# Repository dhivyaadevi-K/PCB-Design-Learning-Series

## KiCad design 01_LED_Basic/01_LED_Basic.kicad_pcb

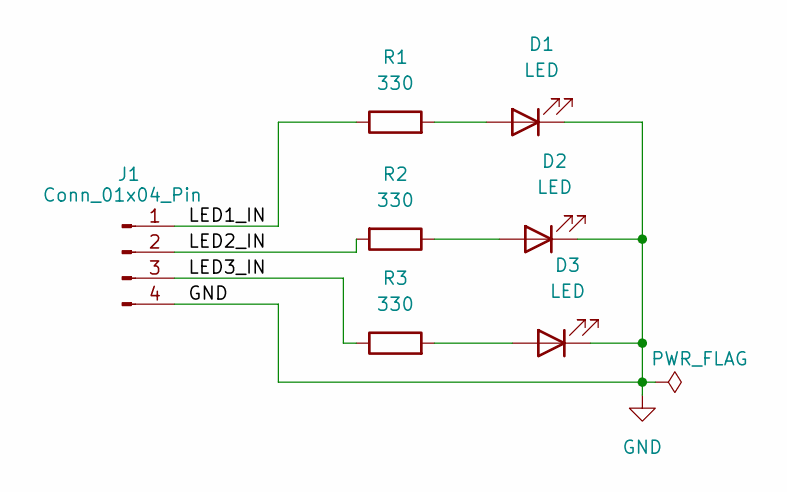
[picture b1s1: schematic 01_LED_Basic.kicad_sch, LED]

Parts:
D1, D2, D3: LED; LED_D5.0mm
J1: Conn_01x04_Pin; PinHeader_1x04_P2.54mm_Vertical
R1, R2, R3: 330; R_Axial_DIN0207_L6.3mm_D2.5mm_P7.62mm_Horizontal

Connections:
/LED1_IN: J1.1, R1.1
/LED2_IN: J1.2, R2.2
/LED3_IN: J1.3, R3.1
GND: D1.1 (K), D2.1 (K), D3.1 (K), J1.4
unnamed: D1.2 (A), R1.2
unnamed: D2.2 (A), R2.1
unnamed: D3.2 (A), R3.2

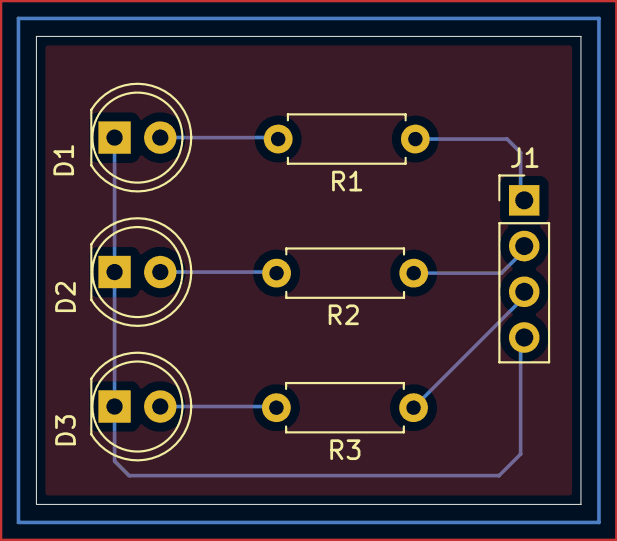
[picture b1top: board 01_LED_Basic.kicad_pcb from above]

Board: 2 copper layers, 30.2 x 26.0 mm, 7 parts (0 on the bottom side), 7 nets.

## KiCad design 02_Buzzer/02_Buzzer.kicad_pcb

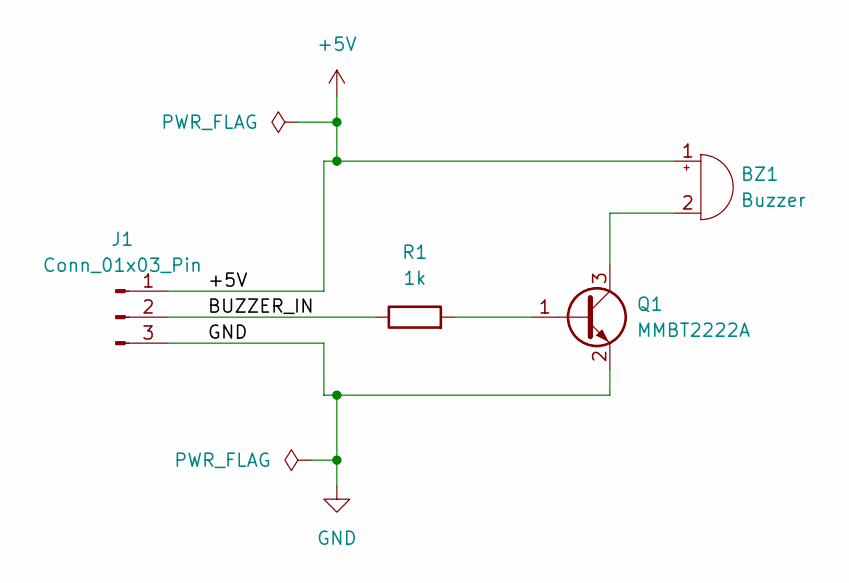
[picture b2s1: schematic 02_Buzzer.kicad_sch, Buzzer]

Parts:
BZ1: Buzzer; Buzzer_12x9.5RM7.6
J1: Conn_01x03_Pin; PinHeader_1x03_P2.54mm_Horizontal
Q1: MMBT2222A; SOT-23
R1: 1k; R_Axial_DIN0207_L6.3mm_D2.5mm_P7.62mm_Horizontal

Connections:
+5V: BZ1.1 (+), J1.1
/BUZZER_IN: J1.2, R1.1
GND: J1.3, Q1.2 (E)
unnamed: BZ1.2 (-), Q1.3 (C)
unnamed: Q1.1 (B), R1.2

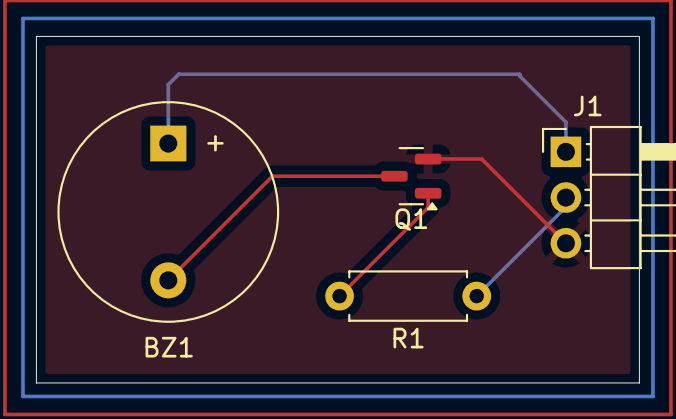
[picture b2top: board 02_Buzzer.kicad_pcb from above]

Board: 2 copper layers, 33.5 x 19.2 mm, 4 parts (0 on the bottom side), 5 nets.

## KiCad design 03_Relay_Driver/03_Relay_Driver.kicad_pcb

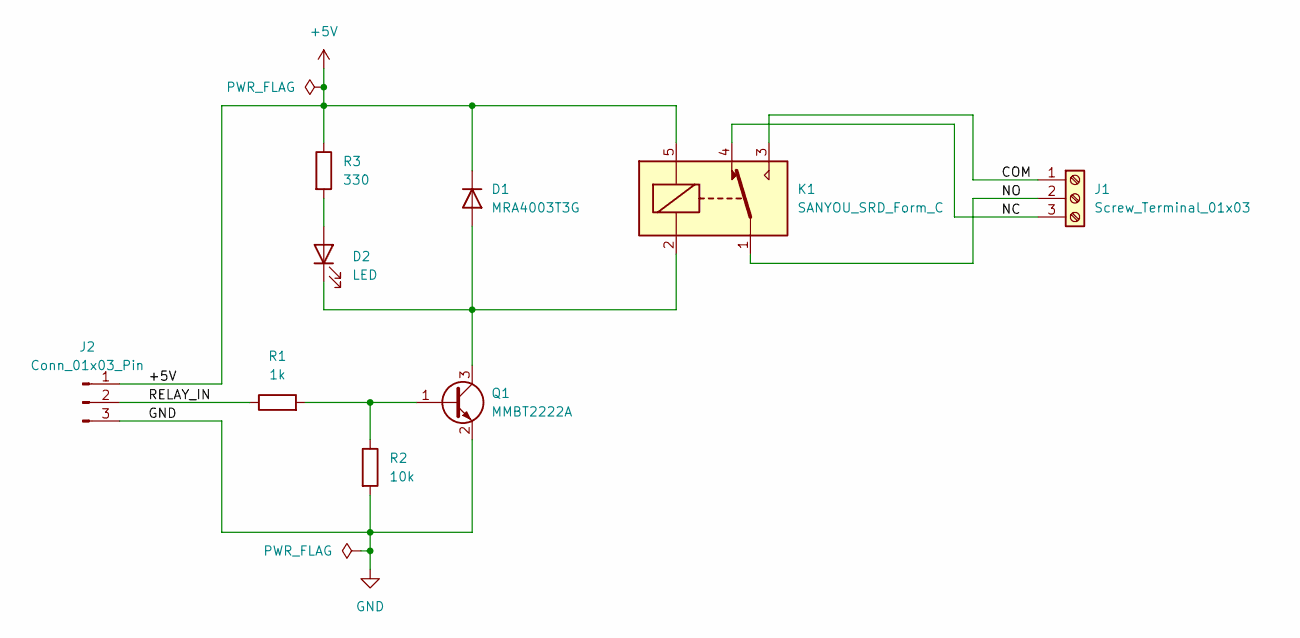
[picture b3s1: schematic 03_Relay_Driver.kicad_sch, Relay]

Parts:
D1: MRA4003T3G; D_SMA
D2: LED; LED_0805_2012Metric
J1: Screw_Terminal_01x03; TerminalBlock_Phoenix_MKDS-1,5-3-5.08_1x03_P5.08mm_Horizont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
J2: Conn_01x03_Pin; PinSocket_1x03_P2.54mm_Vertical
K1: SANYOU_SRD_Form_C; Relay_SPDT_SANYOU_SRD_Series_Form_C
Q1: MMBT2222A; SOT-23
R1: 1k; R_0805_2012Metric
R2: 10k; R_0805_2012Metric
R3: 330; R_0805_2012Metric

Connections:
+5V: D1.1 (K), J2.1, K1.5, R3.1
/COM: J1.1, K1.3
/NC: J1.3, K1.4
/NO: J1.2, K1.1
/RELAY_IN: J2.2, R1.1
GND: J2.3, Q1.2 (E), R2.2
unnamed: D1.2 (A), D2.1 (K), K1.2, Q1.3 (C)
unnamed: D2.2 (A), R3.2
unnamed: Q1.1 (B), R1.2, R2.1

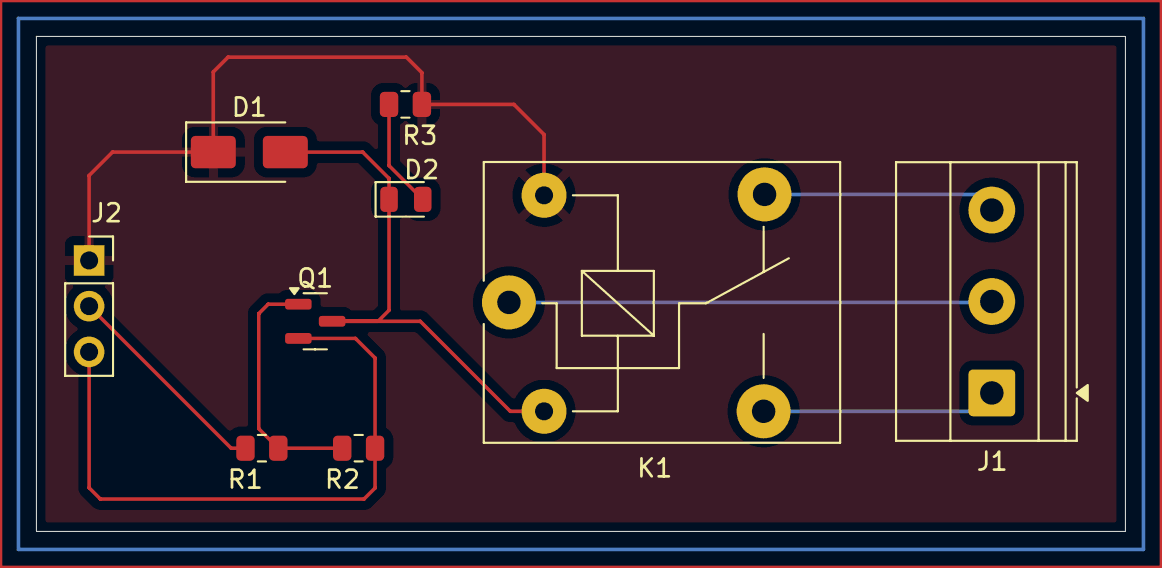
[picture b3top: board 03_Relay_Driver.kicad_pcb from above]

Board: 2 copper layers, 60.5 x 27.5 mm, 9 parts (0 on the bottom side), 9 nets.

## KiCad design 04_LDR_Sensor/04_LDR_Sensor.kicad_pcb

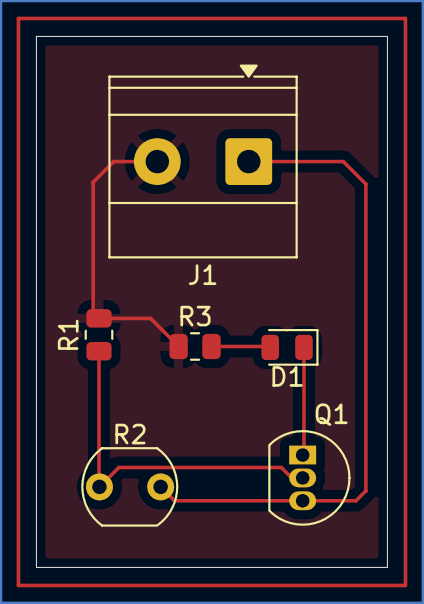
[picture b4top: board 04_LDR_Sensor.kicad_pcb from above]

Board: 2 copper layers, 19.5 x 29.5 mm, 6 parts (0 on the bottom side), 5 nets.

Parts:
D1: LED; LED_0805_2012Metric
J1: Screw_Terminal_01x02; TerminalBlock_Phoenix_MKDS-1,5-2-5.08_1x02_P5.08mm_Horizont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
Q1: BC547; TO-92_Inline
R1, R3: R; R_0805_2012Metric
R2: LDR07; R_LDR_5.1x4.3mm_P3.4mm_Vertical

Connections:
+5V: J1.2, R1.1, R3.1
GND: J1.1, Q1.3 (E), R2.2
unnamed: D1.2 (A), R3.2
unnamed: D1.1 (K), Q1.1 (C)
unnamed: Q1.2 (B), R1.2, R2.1
